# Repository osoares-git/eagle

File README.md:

# eagle
Projetos realizados no cadsoft eagle para fabricação de placas de circuito impresso

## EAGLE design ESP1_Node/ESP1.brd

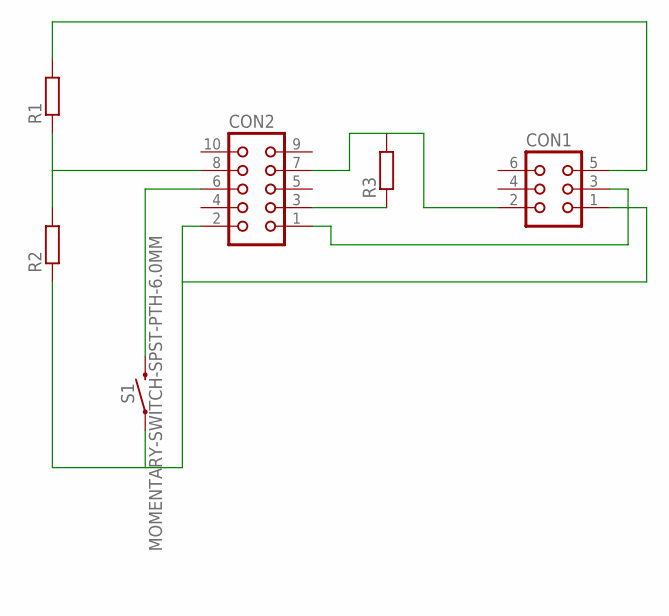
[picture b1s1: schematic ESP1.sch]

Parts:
CON1: CON06L
CON2: CON10L
R1, R2, R3: R-EU_0204/7; 0204/7
S1: MOMENTARY-SWITCH-SPST-PTH-6.0MM; TACTILE_SWITCH_PTH_6.0MM

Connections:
unnamed: CON1.1, CON2.2, R2.1, S1.1
unnamed: CON2.8, R1.1, R2.2
unnamed: CON1.5, R1.2
unnamed: CON1.3, CON2.1
unnamed: CON2.3, R3.1
unnamed: CON1.2, CON2.7, R3.2
unnamed: CON2.6, S1.3 (2)

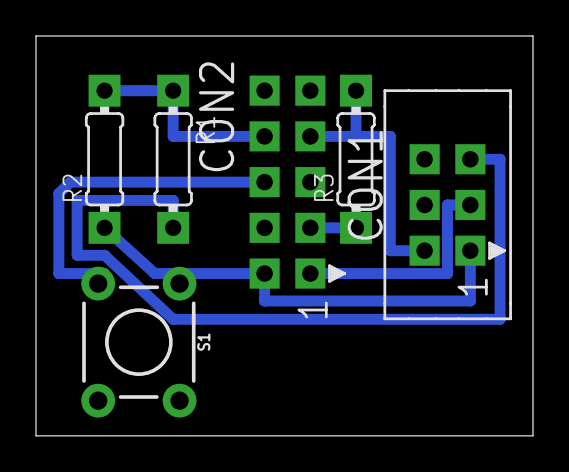
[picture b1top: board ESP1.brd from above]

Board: 2 copper layers, 27.6 x 22.2 mm, 6 parts (0 on the bottom side), 7 nets.

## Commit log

2024-02-01 first release

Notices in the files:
parts and their libraries:
SparkFun-Switches: Licensing: Creative Commons ShareAlike 4.0 International - https://creativecommons.org/licenses/by-sa/4.0
